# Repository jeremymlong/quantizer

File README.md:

# Dual Quantizer

## Specs
 * Range 0 to 5V
 * Arduino Nano based
 * Encoder knob for selecting scale
 * Encoder button for selecting which quantizer is displayed on the LEDs
 * Transpose with CV control
 * Portamento with CV control
 * LED for displaying
    * Red for left quantizer, Green for right quantizer
    * Trigger in
    * Current scale
    * Current CV note out
 * Two quantizers
    * CV input
    * CV output
    * Trigger in - CV input is sampled on rising edge and output until next trigger.
    * Trigger out - A pulse out each time the CV output changes
 * Scales
    * Major
    * Minor natural
    * Minor harmonic
    * Pentatonic major
    * Pentatonic minor
    * Blues major
    * Blues minor
    * Chromatic

## Calibration
Use a multimeter to calibrate the voltage reference to 5.0V. This voltage reference is used by the Arduino and the MCP4921s. The easiest place to measure this is at the AREF socket. This can be done when doing other voltage tests when first applying power to the board.
1. Apply power to the board
1. Connect a multimeter to monitor AREF
1. Adjust the trim pot until the voltage reads 5.0V.

## BOM
| Part | Quantity | Link |
|-----|-----|-----|
| Arduino Nano | 1 | [Tayda](https://www.taydaelectronics.com/nano-3-0-controller-compatible-with-arduino-nano-usb-driver.html) |
| MCP4921 DIP-8 | 2 | [Mouser](https://www.mouser.com/ProductDetail/Microchip-Technology/MCP4921-E-P?qs=1zyQUV6YKYz%252BhdPnOOm6sg%3D%3D), [Digikey](https://www.digikey.com/en/products/detail/microchip-technology/MCP4921-E-P/716280) |
| TL072 DIP-8 | 1 | [Tayda](https://www.taydaelectronics.com/tl072-low-noise-j-fet-dual-op-amp-ic.html) |
| TL431 TO-92 | 1 | [Tayda](https://www.taydaelectronics.com/tl431acl-tl431-precision-shunt-regulator.html) |
| 2N3904 TO-92 | 4 | [Tayda](https://www.taydaelectronics.com/2n3904-npn-general-propose-transistor.html) |
| 5mm WS2811 F5 LED | 13 | [AliExpress](https://www.aliexpress.us/item/2251832527100547.html?gatewayAdapt=glo2usa4itemAdapt), [ebay](https://www.ebay.com/itm/225210423475?itmmeta=01HS53S4ZVHJHBY52T8WQZB1ET&hash=item346f9658b3:g:pUQAAOSwwGdf8ocz&itmprp=enc%3AAQAJAAAAwCDUYGcz5qj68xjJYhneY0VaI0AsSksXRR7zNsdxxVYPv%2BTpHbM6i6Cse7igi7r5pkI4ketezPmbqDTaU3huAlq58YY7W5qptqD56XkPZG7GSnOwLtegVyQoB51Hfvr%2BzgxCyjLdDuAnd0qzc8QuIPkxoM4O4NsTp0nrkO%2FBAysmSOFaF0JAeZIQaoKVNi9e1xnuLqgQoH9CKrZYwR4DYm8v4WXOQEnFtDER7cRtcld9aYo08zqe6yW89MqrQOQFFA%3D%3D%7Ctkp%3ABk9SR4jQ5KPJYw)|
| 1x2 vertical pin header | 1 | [Tayda](https://www.taydaelectronics.com/40-pin-male-2-54-mm-single-row-pin-header-break-away-round-pin-gold-plated.html) |
| 1x4 vertical pin header | 1 | [Tayda](https://www.taydaelectronics.com/40-pin-male-2-54-mm-single-row-pin-header-break-away-round-pin-gold-plated.html) |
| 1x5 vertical pin header | 2 | [Tayda](https://www.taydaelectronics.com/40-pin-male-2-54-mm-single-row-pin-header-break-away-round-pin-gold-plated.html) |
| 1x2 vertical pin socket | 1 | [Tayda](https://www.taydaelectronics.com/2-pin-2-54-mm-single-row-female-pin-header.html) |
| 1x4 vertical pin socket | 1 | [Tayda](https://www.taydaelectronics.com/4-pin-2-54-mm-single-row-female-pin-header.html) |
| 1x5 vertical pin socket | 2 | [Tayda](https://www.taydaelectronics.com/5-pin-2-54-mm-single-row-female-pin-header.html) |
| Rotary encoder (footprint is Alps EC12E) | 1 | [Tayda](https://www.taydaelectronics.com/rotary-encoder-11mm-20-detents-d-shaft-with-switch-vertical.html) |
| 9mm vertical potentiometer 50k | 2 | [Tayda](https://www.taydaelectronics.com/50k-ohm-linear-taper-potentiometer-round-shaft-pcb-9mm.html) |
| Potentiometer 3296W 1k | 1 | [Tayda](https://www.taydaelectronics.com/1k-ohm-trimmer-potentiometer-cermet-25-turns-3296w.html) |
| 330 1/4W resisitor | 1 | [Tayda](https://www.taydaelectronics.com/330-ohm-1-4w-1-metal-film-resistor.html) |
| 1k 1/4W resisitor | 2 | [Tayda](https://www.taydaelectronics.com/10-x-resistor-1k-ohm-1-4w-1-metal-film-pkg-of-10.html) |
| 5.1k 1/4W resisitor | 2 | [Tayda](https://www.taydaelectronics.com/resistor-5-1k-ohm-1-4w-1-metal-film-pkg-of-10.html) |
| 10k 1/4W resisitor | 4 | [Tayda](https://www.taydaelectronics.com/10-x-resistor-10k-ohm-1-4w-1-metal-film-pkg-of-10.html) |
| 15k 1/4W resisitor | 2 | [Tayda](https://www.taydaelectronics.com/10-x-resistor-15k-ohm-1-4w-1-metal-film-pkg-of-10.html) |
| 33k 1/4W resisitor | 2 | [Tayda](https://www.taydaelectronics.com/resistor-33k-ohm-1-4w-1-metal-film-pkg-of-10.html) |
| 100k 1/4W resisitor | 6 | [Tayda](https://www.taydaelectronics.com/10-x-resistor-100k-ohm-1-4w-1-metal-film-pkg-of-10.html) |
| 10nF capacitor 5mm spacing | 2 | [Tayda](https://www.taydaelectronics.com/10nf-0-01uf-100v-5-polyester-film-box-type-capacitor.html) |
| 100nF capacitor 5mm spacing | 7 | [Tayda](https://www.taydaelectronics.com/0-1uf-100v-5-polyester-film-box-type-capacitor.html) |
| 10uF capacitor 5mm diameter, 2mm spacing | 2 | [Tayda](https://www.taydaelectronics.com/10uf-50v-105c-jrb-radial-electrolytic-capacitor-5x11mm.html) |
| PJ301M or PJ-3001F (Thonkiconn) | 10 | [Tayda](https://www.taydaelectronics.com/pj-3001f-3-5-mm-mono-phone-jack.html) |
| 2x5 IDC Shrouded header (no reverse power protection on this) | 1 | [Tayda](https://www.taydaelectronics.com/10-pin-box-header-connector-2-54mm.html) |
| Schottky diode DO-35 (signal diodes work too) | 8 | [Tayda](https://www.taydaelectronics.com/1n5819-schottky-barrier-diode-1a-40v.html) |
| Knobs | 3 | [Tayda](https://www.taydaelectronics.com/knob-davies-1900h-clone-cream.html) |

## TODO
 * Editable scale
 * Chord mode

## Arduino Dependencies
 * [Adafruit_NeoPixel](https://github.com/adafruit/Adafruit_NeoPixel)
 * [AUnit](https://github.com/bxparks/AUnit) (for tests)

## Notes about LEDs
The 12 scale LED are not included on the schematic or board. My hope was to use these boards for another project. I directly mounted the LEDs to the panel with hot glue and wired them point to point. Wires are connected to the leads of the first LED. On the back of the board I left the leads long and connected the power wires as pictured below. The second LED is at the bottom of the panel and the rest wire up the panel to the top.

### Reversing LED order
You can reverse the LED order if you want the lowest note at the top of the panel. There's a define commented out at the top of leds.cpp `REVERSE_LED_ORDER`. Just uncomment that line to reverse the order.

LEDs are WS2811 (NeoPixel) style, but in a traditional 5mm form factor.

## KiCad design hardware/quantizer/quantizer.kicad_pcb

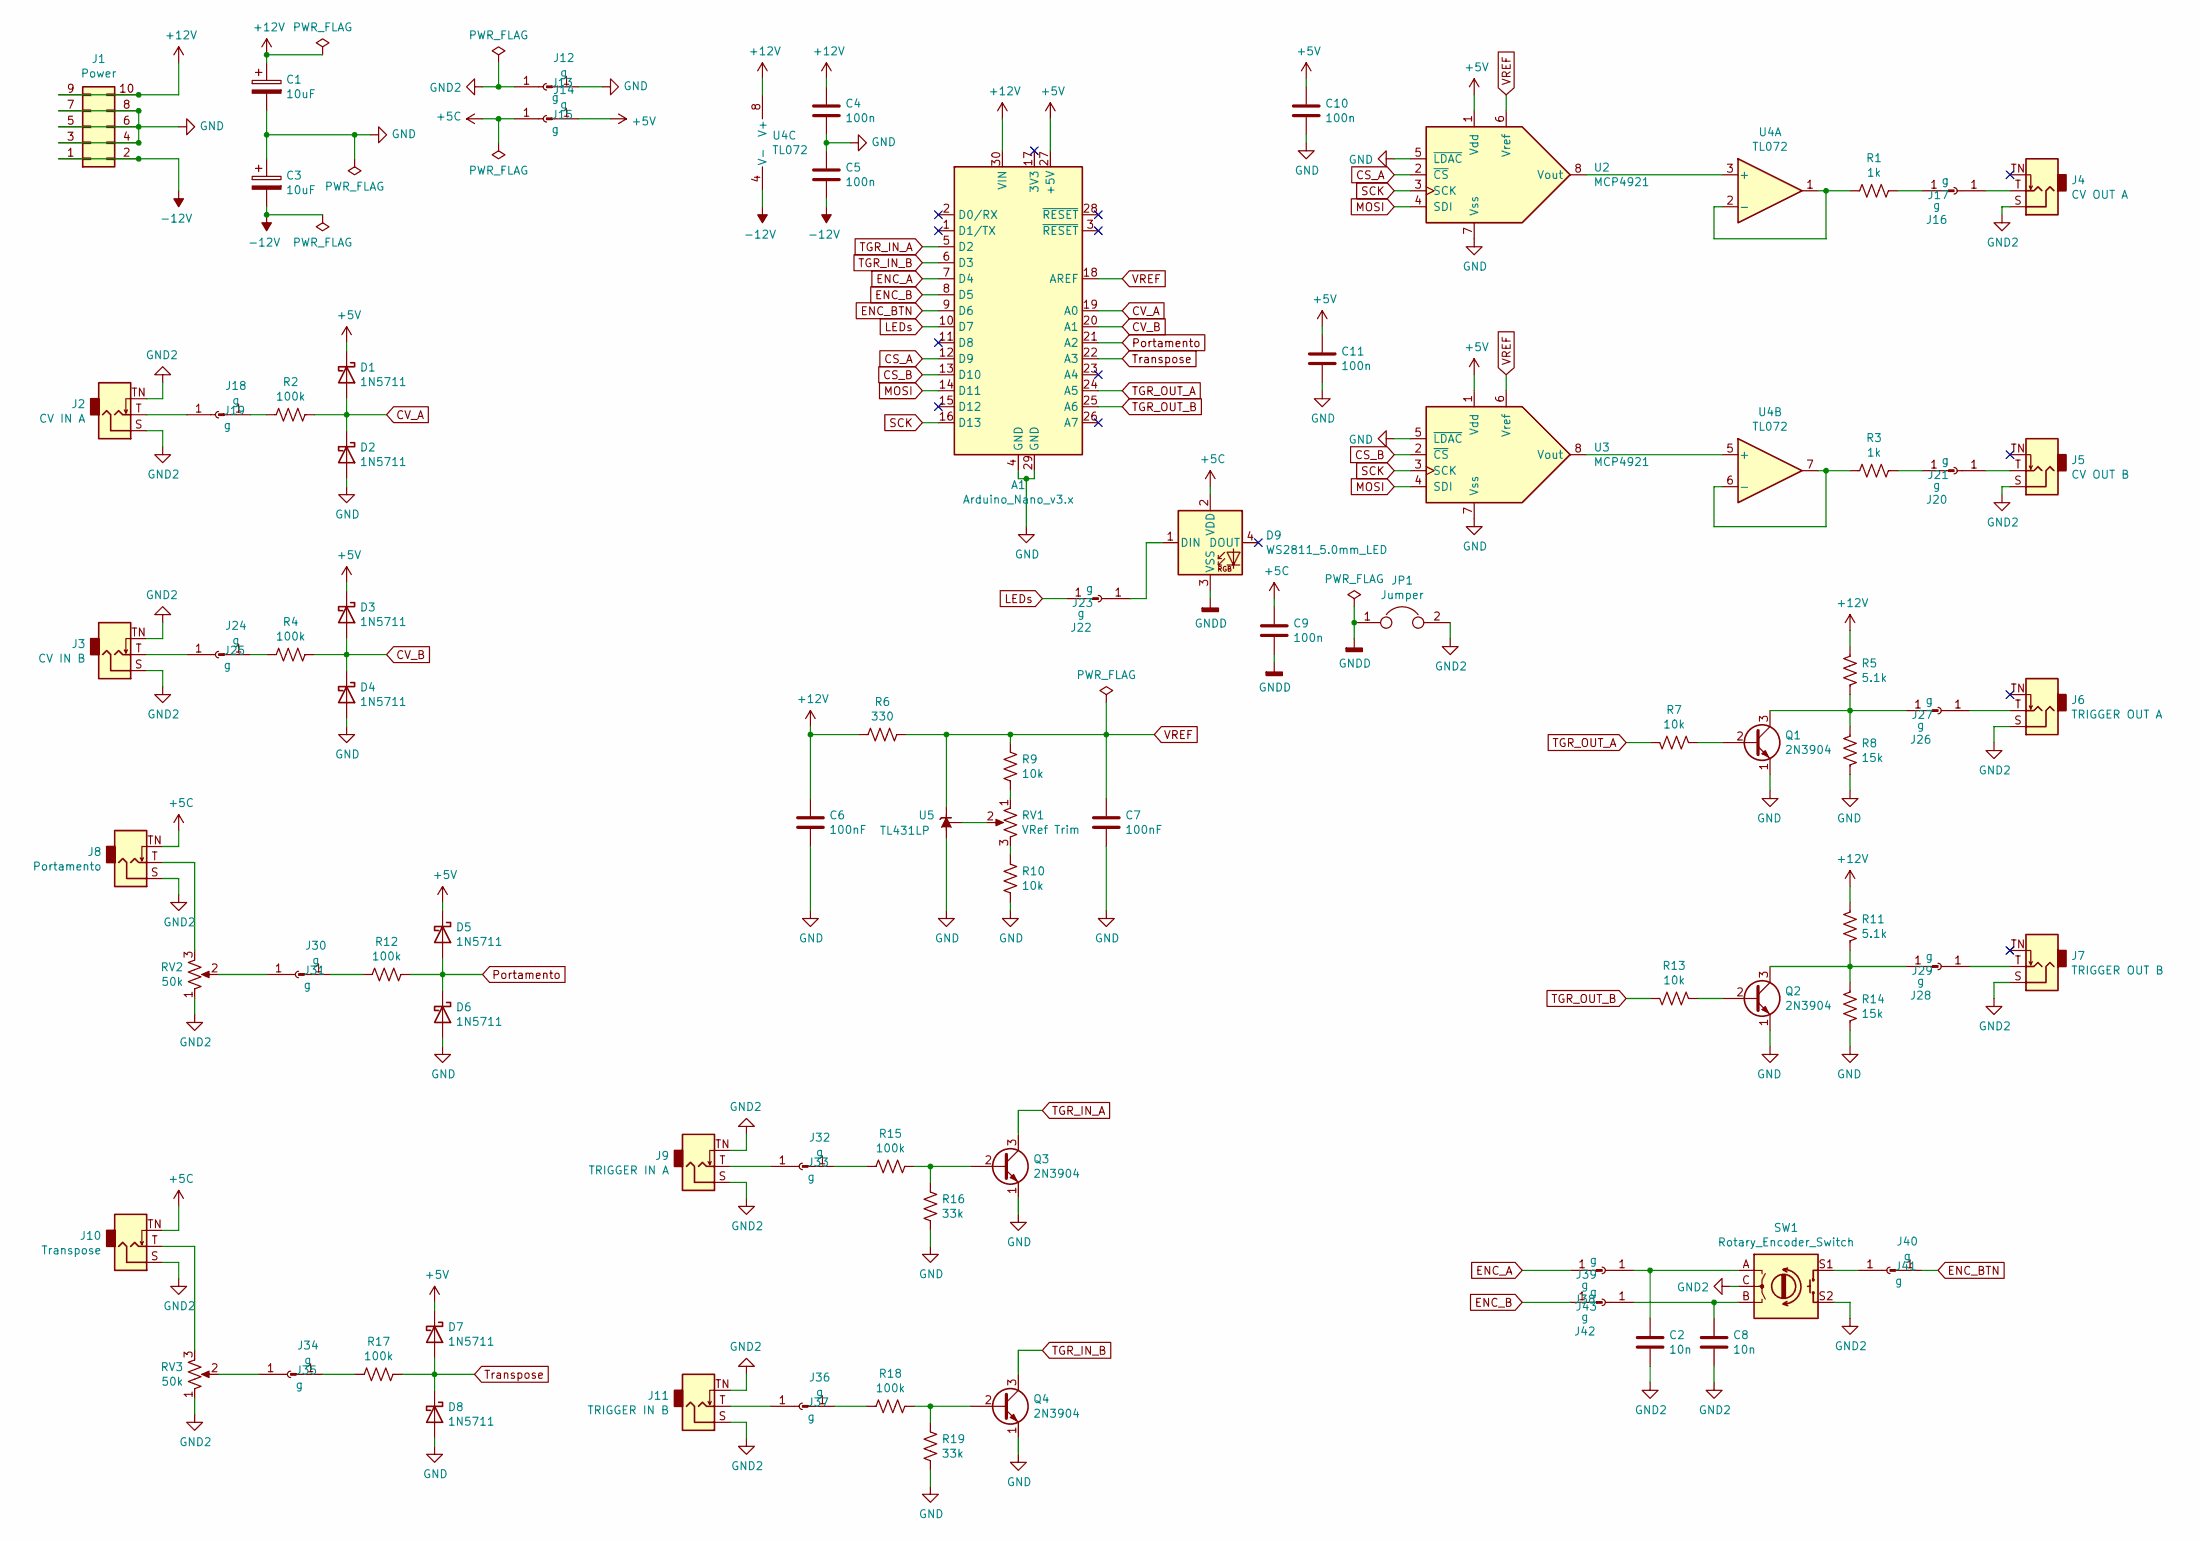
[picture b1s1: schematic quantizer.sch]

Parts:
A1: Arduino_Nano_v3.x; Arduino_Nano
C1, C3: 10uF; CP_Radial_D5.0mm_P2.00mm
C2, C8: 10n; C_Disc_D4.3mm_W1.9mm_P5.00mm
C4, C5, C9, C10, C11: 100n; C_Disc_D4.3mm_W1.9mm_P5.00mm
C6, C7: 100nF; C_Disc_D4.3mm_W1.9mm_P5.00mm
D1, D2, D3, D4, D5, D6, D7, D8: 1N5711; D_DO-35_SOD27_P7.62mm_Horizontal
D9: WS2811_5.0mm_LED; LED_D5.0mm-WS2811
J1: Power; IDC-Header_2x05_P2.54mm_Vertical
J2: CV IN A; Jack_3.5mm_QingPu_WQP-PJ398SM_Vertical_CircularHoles
J3: CV IN B; Jack_3.5mm_QingPu_WQP-PJ398SM_Vertical_CircularHoles
J4: CV OUT A; Jack_3.5mm_QingPu_WQP-PJ398SM_Vertical_CircularHoles
J5: CV OUT B; Jack_3.5mm_QingPu_WQP-PJ398SM_Vertical_CircularHoles
J6: TRIGGER OUT A; Jack_3.5mm_QingPu_WQP-PJ398SM_Vertical_CircularHoles
J7: TRIGGER OUT B; Jack_3.5mm_QingPu_WQP-PJ398SM_Vertical_CircularHoles
J8: Portamento; Jack_3.5mm_QingPu_WQP-PJ398SM_Vertical_CircularHoles
J9: TRIGGER IN A; Jack_3.5mm_QingPu_WQP-PJ398SM_Vertical_CircularHoles
J10: Transpose; Jack_3.5mm_QingPu_WQP-PJ398SM_Vertical_CircularHoles
J11: TRIGGER IN B; Jack_3.5mm_QingPu_WQP-PJ398SM_Vertical_CircularHoles
J12, J13, J14, J15, J16, J17, J18, J19, J20, J21, J22, J23, J24, J25, J26, J27, J28, J29, J30, J31, J32, J33, J34, J35, J36, J37, J38, J39, J40, J41, J42, J43: g; PinHeader_1x01_P2.54mm_Vertical
JP1: Jumper; SolderJumper-2_P1.3mm_Bridged2Bar_Pad1.0x1.5mm
Q1, Q2, Q3, Q4: 2N3904; TO-92_Inline
R1, R3: 1k; R_Axial_DIN0207_L6.3mm_D2.5mm_P7.62mm_Horizontal
R2, R4, R12, R15, R17, R18: 100k; R_Axial_DIN0207_L6.3mm_D2.5mm_P7.62mm_Horizontal
R5, R11: 5.1k; R_Axial_DIN0207_L6.3mm_D2.5mm_P7.62mm_Horizontal
R6: 330; R_Axial_DIN0207_L6.3mm_D2.5mm_P7.62mm_Horizontal
R7, R9, R10, R13: 10k; R_Axial_DIN0207_L6.3mm_D2.5mm_P7.62mm_Horizontal
R8, R14: 15k; R_Axial_DIN0207_L6.3mm_D2.5mm_P7.62mm_Horizontal
R16, R19: 33k; R_Axial_DIN0207_L6.3mm_D2.5mm_P7.62mm_Horizontal
RV1: VRef Trim; Potentiometer_Bourns_3296W_Vertical
RV2, RV3: 50k; Potentiometer_Alpha_RD901F-40-00D_Single_Vertical_CircularH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
SW1: Rotary_Encoder_Switch; RotaryEncoder_Alps_EC12E-Switch_Vertical_H20mm
U2, U3: MCP4921; DIP-8_W7.62mm_LongPads
U4: TL072; DIP-8_W7.62mm_Socket_LongPads
U5: TL431LP; TO-92_Inline

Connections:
+5C: C9.1, D9.2 (VDD), J8.TN, J10.TN, J15.1
+5V: A1.27 (+5V), C10.1, C11.1, D1.1 (K), D3.1 (K), D5.1 (K), D7.1 (K), J14.1, U2.1 (Vdd), U3.1 (Vdd)
+12V: A1.30 (VIN), C1.1, C4.1, C6.1, J1.9, J1.10, R5.1, R6.1, R11.1, U4.8 (V+)
-12V: C3.2, C5.2, J1.1, J1.2, U4.4 (V-)
CS_A: A1.12 (D9), U2.2 (~CS)
CS_B: A1.13 (D10), U3.2 (~CS)
CV_A: A1.19 (A0), D1.2 (A), D2.1 (K), R2.2
CV_B: A1.20 (A1), D3.2 (A), D4.1 (K), R4.2
ENC_A: A1.7 (D4), J38.1
ENC_B: A1.8 (D5), J42.1
ENC_BTN: A1.9 (D6), J40.1
GND: A1.4 (GND), A1.29 (GND), C1.2, C3.1, C4.2, C5.1, C6.2, C7.2, C10.2, C11.2, D2.2 (A), D4.2 (A), D6.2 (A), D8.2 (A), J1.3, J1.4, J1.5, J1.6, J1.7, J1.8, J12.1, Q1.1 (E), Q2.1 (E), Q3.1 (E), Q4.1 (E), R8.2, R10.1, R14.2, R16.2, R19.2, U2.5 (~LDAC), U2.7 (Vss), U3.5 (~LDAC), U3.7 (Vss), U5.2 (A)
GND2: C2.2, C8.2, J2.S, J2.TN, J3.S, J3.TN, J4.S, J5.S, J6.S, J7.S, J8.S, J9.S, J9.TN, J10.S, J11.S, J11.TN, J13.1, JP1.2, RV2.1, RV3.1, SW1.C, SW1.S2
GNDD: C9.2, D9.3 (VSS), JP1.1
LEDs: A1.10 (D7), J22.1
MOSI: A1.14 (D11), U2.4 (SDI), U3.4 (SDI)
unnamed: C2.1, J39.1, SW1.A
unnamed: C8.1, J43.1, SW1.B
unnamed: D9.1 (DIN), J23.1
unnamed: J8.T, RV2.3
unnamed: J10.T, RV3.3
unnamed: J11.T, J37.1
unnamed: J16.1, R1.2
unnamed: J4.T, J17.1
unnamed: J18.1, R2.1
unnamed: J2.T, J19.1
unnamed: J20.1, R3.2
unnamed: J5.T, J21.1
unnamed: J24.1, R4.1
unnamed: J3.T, J25.1
unnamed: J26.1, Q1.3 (C), R5.2, R8.1
unnamed: J6.T, J27.1
unnamed: J28.1, Q2.3 (C), R11.2, R14.1
unnamed: J7.T, J29.1
unnamed: J30.1, R12.1
unnamed: J31.1, RV2.2
unnamed: J32.1, R15.1
unnamed: J9.T, J33.1
unnamed: J34.1, R17.1
unnamed: J35.1, RV3.2
unnamed: J36.1, R18.1
unnamed: J41.1, SW1.S1
unnamed: Q1.2 (B), R7.1
unnamed: Q2.2 (B), R13.1
unnamed: Q3.2 (B), R15.2, R16.1
unnamed: Q4.2 (B), R18.2, R19.1
unnamed: R1.1, U4.1, U4.2 (-)
unnamed: R3.1, U4.6 (-), U4.7
unnamed: R9.1, RV1.1
unnamed: R10.2, RV1.3
unnamed: RV1.2, U5.1 (REF)
unnamed: U2.8 (Vout), U4.3 (+)
unnamed: U3.8 (Vout), U4.5 (+)
Portamento: A1.21 (A2), D5.2 (A), D6.1 (K), R12.2
SCK: A1.16 (D13), U2.3 (SCK), U3.3 (SCK)
TGR_IN_A: A1.5 (D2), Q3.3 (C)
TGR_IN_B: A1.6 (D3), Q4.3 (C)
TGR_OUT_A: A1.24 (A5), R7.2
Transpose: A1.22 (A3), D7.2 (A), D8.1 (K), R17.2
VREF: A1.18 (AREF), C7.1, R6.2, R9.2, U2.6 (Vref), U3.6 (Vref), U5.3 (K)

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
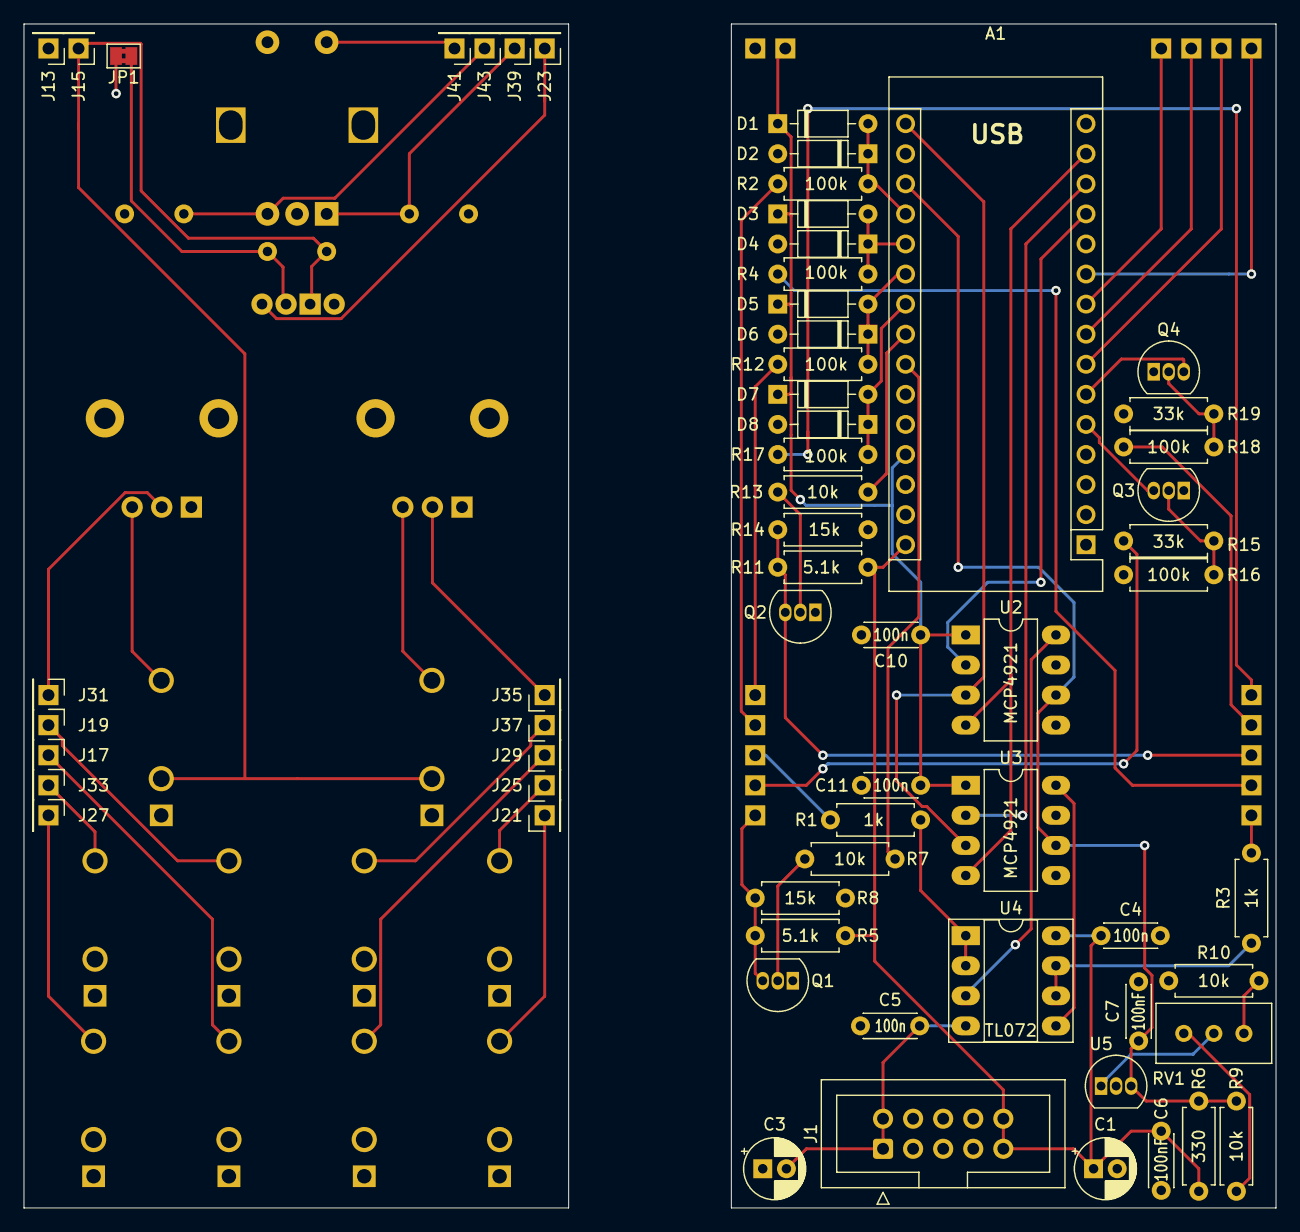
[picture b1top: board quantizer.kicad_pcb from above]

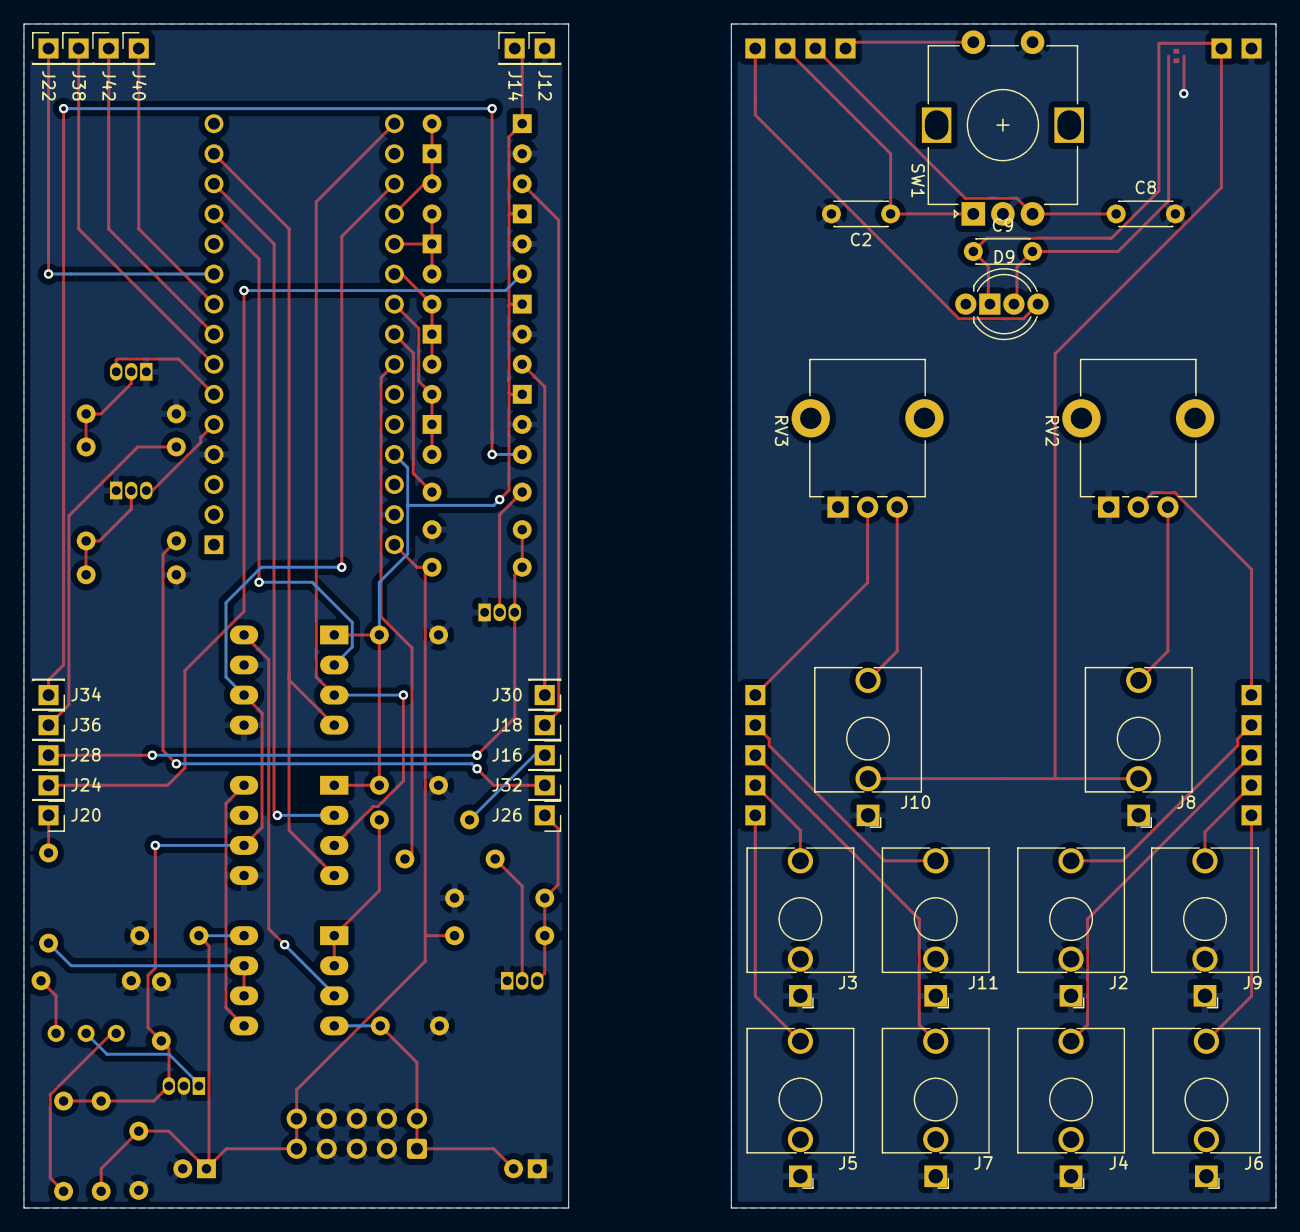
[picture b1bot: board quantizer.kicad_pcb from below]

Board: 2 copper layers, 105.7 x 100.0 mm, 96 parts (33 on the bottom side), 61 nets.

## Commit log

2024-03-11 Fix transpose weirdness
2024-03-12 Fixed trigger in issue
2024-03-13 Trigger in fix
2024-03-13 Updated brd/sch pin change, added photos
2024-03-14 cleanup
2024-03-14 Added readme
2024-03-14 Updated dependencies in README
2024-03-15 Updated README: BOM, calibration and LEDs
2024-03-15 More LED description
2024-03-15 Create LICENSE
2024-03-17 Added links to BOM
2024-03-17 Added quantizer-cache.lib and PDF of schematic
2024-04-07 Added reverse LED order option
2024-04-07 Clarification about LED order
